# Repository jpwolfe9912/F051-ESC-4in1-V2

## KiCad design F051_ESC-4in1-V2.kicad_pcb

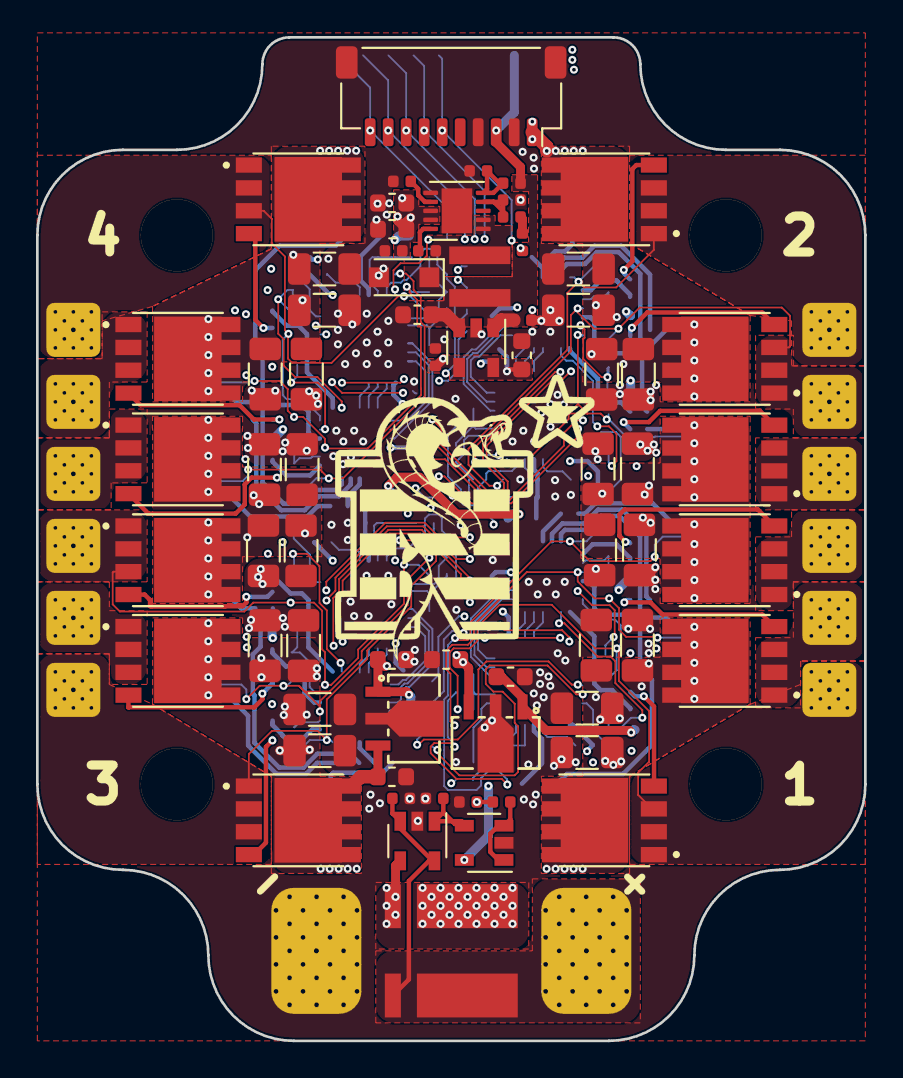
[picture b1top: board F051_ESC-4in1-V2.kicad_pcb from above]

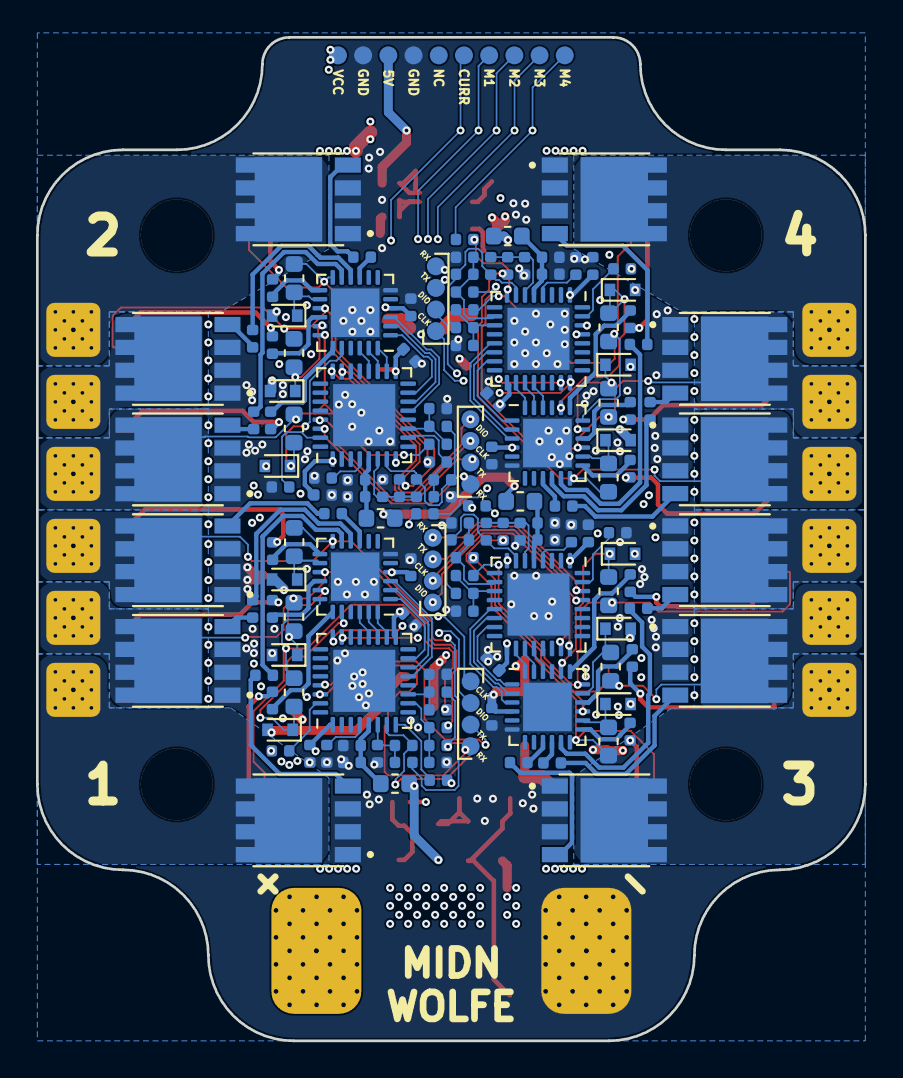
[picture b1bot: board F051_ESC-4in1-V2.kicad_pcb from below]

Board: 4 copper layers, 46.0 x 55.8 mm, 223 parts (149 on the bottom side), 164 nets.

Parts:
C1, C7, C13, C14, C15, C25, C26, C27, C28, C34, C35, C36, C37, C41, C47, C48, C49, C70, C74: 0.1uF; C_0402_1005Metric
C2, C3, C5, C6, C29, C30, C31, C38, C39, C40, C42, C43, C44, C69: 0.1uF; C_0603_1608Metric
C4, C68: 0.33uF; C_0603_1608Metric
C8: 3.3nF; C_0402_1005Metric
C9, C11, C23, C32, C45: 10nF; C_0402_1005Metric
C10, C12, C22, C33, C46: 1uF; C_0402_1005Metric
C16, C17, C18, C19, C20, C21, C50, C51, C52, C53, C54, C55, C56, C57, C58, C59, C60, C61, C62, C63, C64, C65, C66, C67: 47uF; C_1206_3216Metric
C24, C72, C73: 2.2uF; C_0603_1608Metric
C71: 22uF; C_0603_1608Metric
C75: 560pF; C_0402_1005Metric
C76: 2pF; C_0402_1005Metric
D1, D2, D3, D4, D5, D6, D7, D8, D9, D10, D11, D12: 250V; D_SOD-523
D13: 50V, 2A; D_SOD-123F
FB1, FB2, FB3, FB4: 100@100MHz; L_0603_1608Metric
H1, H2, H3, H4: MountingHole_Pad; MountingHole_4in1ESC
J1: Conn_01x02; Conn_PowerPad_4in1
J2: Conn_01x10; JST_SH_SM10B-SRSS-TB_1x10-1MP_P1.00mm_Horizontal
J3, J4, J5, J7: Conn_01x04; Conn_Debug
J6, J8, J10, J11: Conn_01x03; Conn_MotorPhase
J9: Conn_01x10; Conn_FC_Solder_10
L1: 12uH; L_XGL4030
Q1, Q2, Q3, Q4, Q5, Q6, Q7, Q8, Q9, Q10, Q11, Q12, Q13, Q14, Q15, Q16, Q17, Q18, Q19, Q20, Q21, Q22, Q23, Q24: TPH1R204PB
R1: 0m30; R_Shunt_Vishay_WSLP2726
R2: 60k; R_0402_1005Metric
R3: 500; R_0402_1005Metric
R4, R5, R6, R13, R14, R16, R17, R18, R19, R22, R26, R27, R38, R39, R40, R41, R43, R44, R61, R62, R63, R64, R66, R67: 10k; R_0402_1005Metric
R7, R8, R9, R10, R11, R12, R32, R33, R34, R35, R36, R37, R49, R50, R51, R52, R53, R54, R55, R56, R57, R58, R59, R60: 10; R_0402_1005Metric
R15, R20, R21, R23, R24, R25, R28, R29, R30, R31, R42, R45, R46, R47, R48, R65, R68, R69, R70, R71: 1k; R_0402_1005Metric
R73: 20k; R_0402_1005Metric
R74: 3.8k; R_0402_1005Metric
R76: 200k; R_0402_1005Metric
R77: 68k; R_0402_1005Metric
U1, U8, U10, U11: FD6288Q; QFN-24-1EP_4x4mm_P0.5mm_EP2.7x2.7mm
U2, U6, U9, U12: STM32F051K6Ux; QFN-32-1EP_5x5mm_P0.5mm_EP3.45x3.45mm
U3, U13: L78L12_SOT89; L78L12ACUTR
U4: LP2985-3.3; SOT-23-5
U5: INA139; SOT-23-5
U7: OPA340NA; SOT-23-5
U14: MP4560_QFN10; DFN-10-1EP_3x3mm_P0.5mm_EP1.7x2.5mm
U15: DTOM; DTOM_L

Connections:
+3.3VA_1: C11.1, C12.1, FB1.1, U2.5
+3.3VA_2: C9.1, C10.1, FB2.1, U6.5
+3.3VA_3: C32.1, C33.1, FB3.1, U9.5
+3.3VA_4: C45.1, C46.1, FB4.1, U12.5
+3V3: C13.1, C14.1, C23.1, C24.1, C25.1, C26.1, C34.1, C35.1, C47.1, C48.1, FB1.2, FB2.2, FB3.2, FB4.2, U2.1, U2.17, U4.4, U4.5, U6.1, U6.17, U7.5, U9.1, U9.17, U12.1, U12.17
+5V: C22.1, C71.1, J2.3, J9.3, L1.2, R73.1, U4.1, U4.3
+12V_1: C37.1, C41.1, C69.1, D7.2, D8.2, D9.2, D10.2, D11.2, D12.2, U10.4, U11.4, U13.1
+12V_2: C1.1, C5.1, C28.1, D1.2, D2.2, D3.2, D4.2, D5.2, D6.2, U1.4, U3.1, U8.4
/Curent Sense/CURR: C8.2, J2.6, J9.6, R3.1
/MCU 3/BOOT0: R48.1, U9.31
/MCU 3/HIN1: U9.18, U10.24
/MCU 3/HIN2: U9.19, U10.23
/MCU 3/LIN1: U9.15, U10.1
/MCU 3/LIN2: U9.14, U10.2
/MCU 3/LIN3: U9.13, U10.3
/MCU 3/NRST: C36.1, U9.4
/MCU 3/PhaseA: C38.2, J11.3, Q13.1, Q13.2, Q13.3, Q14.5, Q14.6, Q14.7, Q14.8, Q14.9, R38.2, U10.18
/MCU 3/PhaseB: C39.2, J11.2, Q15.1, Q15.2, Q15.3, Q16.5, Q16.6, Q16.7, Q16.8, Q16.9, R40.2, U10.15
/MCU 3/PhaseC: C40.2, J11.1, Q17.1, Q17.2, Q17.3, Q18.5, Q18.6, Q18.7, Q18.8, Q18.9, R43.2, U10.12
/MCU 3/SWCLK: J4.2, U9.24
/MCU 3/SWDIO: J4.1, U9.23
/MCU 3/SenseA: R38.1, R39.1, R45.2, U9.11
/MCU 3/SenseB: R40.1, R41.1, R46.2, U9.10
/MCU 3/SenseC: R43.1, R44.1, R47.2, U9.6
/MCU 3/SenseCOM: R39.2, R41.2, R44.2, U9.7
/MCU 3/USART1_RX: J4.4, U9.30
/MCU 3/USART1_TX: J4.3, U9.29
/MCU_1/BOOT0: R24.1, U2.31
/MCU_1/HIN1: U1.24, U2.18
/MCU_1/HIN2: U1.23, U2.19
/MCU_1/LIN1: U1.1, U2.15
/MCU_1/LIN2: U1.2, U2.14
/MCU_1/LIN3: U1.3, U2.13
/MCU_1/NRST: C15.1, U2.4
/MCU_1/PhaseA: C2.2, J6.3, Q1.1, Q1.2, Q1.3, Q2.5, Q2.6, Q2.7, Q2.8, Q2.9, R13.2, U1.18
/MCU_1/PhaseB: C3.2, J6.2, Q3.1, Q3.2, Q3.3, Q4.5, Q4.6, Q4.7, Q4.8, Q4.9, R16.2, U1.15
/MCU_1/PhaseC: C6.2, J6.1, Q5.1, Q5.2, Q5.3, Q6.5, Q6.6, Q6.7, Q6.8, Q6.9, R18.2, U1.12
/MCU_1/SWCLK: J3.1, U2.24
/MCU_1/SWDIO: J3.2, U2.23
/MCU_1/SenseA: R13.1, R14.1, R20.2, U2.11
/MCU_1/SenseB: R16.1, R17.1, R21.2, U2.10
/MCU_1/SenseC: R18.1, R19.1, R23.2, U2.6
/MCU_1/SenseCOM: R14.2, R17.2, R19.2, U2.7
/MCU_1/USART1_RX: J3.4, U2.30
/MCU_1/USART1_TX: J3.3, U2.29
/MCU_2/BOOT0: R31.1, U6.31
/MCU_2/HIN1: U6.18, U8.24
/MCU_2/HIN2: U6.19, U8.23
/MCU_2/LIN1: U6.15, U8.1
/MCU_2/LIN2: U6.14, U8.2
/MCU_2/LIN3: U6.13, U8.3
/MCU_2/NRST: C27.1, U6.4
/MCU_2/PhaseA: C29.2, J8.3, Q7.1, Q7.2, Q7.3, Q8.5, Q8.6, Q8.7, Q8.8, Q8.9, R4.2, U8.18
/MCU_2/PhaseB: C30.2, J8.2, Q9.1, Q9.2, Q9.3, Q10.5, Q10.6, Q10.7, Q10.8, Q10.9, R6.2, U8.15
/MCU_2/PhaseC: C31.2, J8.1, Q11.1, Q11.2, Q11.3, Q12.5, Q12.6, Q12.7, Q12.8, Q12.9, R26.2, U8.12
/MCU_2/SWCLK: J5.2, U6.24
/MCU_2/SWDIO: J5.1, U6.23
/MCU_2/SenseA: R4.1, R5.1, R28.2, U6.11
/MCU_2/SenseB: R6.1, R22.1, R29.2, U6.10
/MCU_2/SenseC: R26.1, R27.1, R30.2, U6.6
/MCU_2/SenseCOM: R5.2, R22.2, R27.2, U6.7
/MCU_2/USART1_RX: J5.4, U6.30
/MCU_2/USART1_TX: J5.3, U6.29
/MCU_4/BOOT0: R71.1, U12.31
/MCU_4/HIN1: U11.24, U12.18
/MCU_4/HIN2: U11.23, U12.19
/MCU_4/LIN1: U11.1, U12.15
/MCU_4/LIN2: U11.2, U12.14
/MCU_4/LIN3: U11.3, U12.13
/MCU_4/NRST: C49.1, U12.4
/MCU_4/PhaseA: C42.2, J10.3, Q19.1, Q19.2, Q19.3, Q20.5, Q20.6, Q20.7, Q20.8, Q20.9, R61.2, U11.18
/MCU_4/PhaseB: C43.2, J10.2, Q21.1, Q21.2, Q21.3, Q22.5, Q22.6, Q22.7, Q22.8, Q22.9, R63.2, U11.15
/MCU_4/PhaseC: C44.2, J10.1, Q23.1, Q23.2, Q23.3, Q24.5, Q24.6, Q24.7, Q24.8, Q24.9, R66.2, U11.12
/MCU_4/SWCLK: J7.1, U12.24
/MCU_4/SWDIO: J7.2, U12.23
/MCU_4/SenseA: R61.1, R62.1, R68.2, U12.11
/MCU_4/SenseB: R63.1, R64.1, R69.2, U12.10
/MCU_4/SenseC: R66.1, R67.1, R70.2, U12.6
/MCU_4/SenseCOM: R62.2, R64.2, R67.2, U12.7
/MCU_4/USART1_RX: J7.4, U12.30
/MCU_4/USART1_TX: J7.3, U12.29
/MOSFET Driver 3/HIN1: U9.20, U10.22
/MOSFET Driver 3/HO1: R49.2, U10.19
/MOSFET Driver 3/HO2: R51.2, U10.16
/MOSFET Driver 3/HO3: R53.2, U10.13
/MOSFET Driver 3/LO1: R50.2, U10.11
/MOSFET Driver 3/LO2: R52.2, U10.10
/MOSFET Driver 3/LO3: R54.2, U10.9
/MOSFET Driver 3/VB1: C38.1, D7.1, U10.20
/MOSFET Driver 3/VB2: C39.1, D8.1, U10.17
/MOSFET Driver 3/VB3: C40.1, D9.1, U10.14
/MOSFET_Driver_1/HIN1: U1.22, U2.20
/MOSFET_Driver_1/HO1: R7.2, U1.19
/MOSFET_Driver_1/HO2: R9.2, U1.16
/MOSFET_Driver_1/HO3: R11.2, U1.13
/MOSFET_Driver_1/LO1: R8.2, U1.11
/MOSFET_Driver_1/LO2: R10.2, U1.10
/MOSFET_Driver_1/LO3: R12.2, U1.9
/MOSFET_Driver_1/VB1: C2.1, D2.1, U1.20
/MOSFET_Driver_1/VB2: C3.1, D3.1, U1.17
/MOSFET_Driver_1/VB3: C6.1, D4.1, U1.14
/MOSFET_Driver_2/HIN1: U6.20, U8.22
/MOSFET_Driver_2/HO1: R32.2, U8.19
/MOSFET_Driver_2/HO2: R34.2, U8.16
/MOSFET_Driver_2/HO3: R36.2, U8.13
/MOSFET_Driver_2/LO1: R33.2, U8.11
/MOSFET_Driver_2/LO2: R35.2, U8.10
/MOSFET_Driver_2/LO3: R37.2, U8.9
/MOSFET_Driver_2/VB1: C29.1, D1.1, U8.20
/MOSFET_Driver_2/VB2: C30.1, D5.1, U8.17
/MOSFET_Driver_2/VB3: C31.1, D6.1, U8.14
/MOSFET_Driver_4/HIN1: U11.22, U12.20
/MOSFET_Driver_4/HO1: R55.2, U11.19
/MOSFET_Driver_4/HO2: R57.2, U11.16
/MOSFET_Driver_4/HO3: R59.2, U11.13
/MOSFET_Driver_4/LO1: R56.2, U11.11
/MOSFET_Driver_4/LO2: R58.2, U11.10
/MOSFET_Driver_4/LO3: R60.2, U11.9
/MOSFET_Driver_4/VB1: C42.1, D10.1, U11.20
/MOSFET_Driver_4/VB2: C43.1, D11.1, U11.17
/MOSFET_Driver_4/VB3: C44.1, D12.1, U11.14
/PWM_1: J2.7, J9.7, R15.2
/PWM_2: J2.8, J9.8, R25.2
/PWM_3: J2.9, J9.9, R42.2
/PWM_4: J2.10, J9.10, R65.2
GND: C1.2, C4.2, C5.2, C7.1, C8.1, C9.2, C10.2, C11.2, C12.2, C13.2, C14.2, C15.2, C16.1, C17.1, C18.1, C19.1, C20.1, C21.1, C22.2, C23.2, C24.2, C25.2, C26.2, C27.2, C28.2, C32.2, C33.2, C34.2, C35.2, C36.2, C37.2, C41.2, C45.2, C46.2, C47.2, C48.2, C49.2, C50.1, C51.1, C52.1, C53.1, C54.1, C55.1, C56.1, C57.1, C58.1, C59.1, C60.1, C61.1, C62.1, C63.1, C64.1, C65.1, C66.1, C67.1, C68.2, C69.2, C71.2, C72.2, C73.2, C74.2, C76.2, D13.2, H1.1, H2.1, H3.1, H4.1, J1.2, J2.2, J2.4, J9.2, J9.4, Q2.1, Q2.2, Q2.3, Q4.1, Q4.2, Q4.3, Q6.1, Q6.2, Q6.3, Q8.1, Q8.2, Q8.3, Q10.1, Q10.2, Q10.3, Q12.1, Q12.2, Q12.3, Q14.1, Q14.2, Q14.3, Q16.1, Q16.2, Q16.3, Q18.1, Q18.2, Q18.3, Q20.1, Q20.2, Q20.3, Q22.1, Q22.2, Q22.3, Q24.1, Q24.2, Q24.3, R2.2, R20.1, R21.1, R23.1, R24.2, R28.1, R29.1, R30.1, R31.2, R45.1, R46.1, R47.1, R48.2, R68.1, R69.1, R70.1, R71.2, R74.2, R76.2, R77.2, U1.6, U1.25, U2.33, U3.2, U4.2, U5.2, U6.33, U7.2, U8.6, U8.25, U9.33, U10.6, U10.25, U11.6, U11.25, U12.33, U13.2, U14.6
unnamed: C70.1, D13.1, L1.1, U14.1, U14.2
unnamed: C70.2, U14.10
unnamed: C75.1, C76.1, U14.4
unnamed: C75.2, R77.1
unnamed: Q1.4, R7.1
unnamed: Q2.4, R8.1
unnamed: Q3.4, R9.1
unnamed: Q4.4, R10.1
unnamed: Q5.4, R11.1
unnamed: Q6.4, R12.1
unnamed: Q7.4, R32.1
unnamed: Q8.4, R33.1
unnamed: Q9.4, R34.1
unnamed: Q10.4, R35.1
unnamed: Q11.4, R36.1
unnamed: Q12.4, R37.1
unnamed: Q13.4, R49.1
unnamed: Q14.4, R50.1
unnamed: Q15.4, R51.1
unnamed: Q16.4, R52.1
unnamed: Q17.4, R53.1
unnamed: Q18.4, R54.1
unnamed: Q19.4, R55.1
unnamed: Q20.4, R56.1
unnamed: Q21.4, R57.1
unnamed: Q22.4, R58.1
unnamed: Q23.4, R59.1
unnamed: Q24.4, R60.1
unnamed: R2.1, U5.1, U7.4
unnamed: R3.2, U7.1, U7.3
unnamed: R15.1, U2.8
unnamed: R25.1, U6.8
unnamed: R42.1, U9.8
unnamed: R65.1, U12.8
unnamed: R73.2, R74.1, U14.5
unnamed: R76.1, U14.7
VCC: C7.2, J1.1, R1.1, U5.3, U5.5
VCC_Shunt: C4.1, C16.2, C17.2, C18.2, C19.2, C20.2, C21.2, C50.2, C51.2, C52.2, C53.2, C54.2, C55.2, C56.2, C57.2, C58.2, C59.2, C60.2, C61.2, C62.2, C63.2, C64.2, C65.2, C66.2, C67.2, C68.1, C72.1, C73.1, C74.1, J2.1, J9.1, Q1.5, Q1.6, Q1.7, Q1.8, Q1.9, Q3.5, Q3.6, Q3.7, Q3.8, Q3.9, Q5.5, Q5.6, Q5.7, Q5.8, Q5.9, Q7.5, Q7.6, Q7.7, Q7.8, Q7.9, Q9.5, Q9.6, Q9.7, Q9.8, Q9.9, Q11.5, Q11.6, Q11.7, Q11.8, Q11.9, Q13.5, Q13.6, Q13.7, Q13.8, Q13.9, Q15.5, Q15.6, Q15.7, Q15.8, Q15.9, Q17.5, Q17.6, Q17.7, Q17.8, Q17.9, Q19.5, Q19.6, Q19.7, Q19.8, Q19.9, Q21.5, Q21.6, Q21.7, Q21.8, Q21.9, Q23.5, Q23.6, Q23.7, Q23.8, Q23.9, R1.2, U3.3, U5.4, U13.3, U14.8, U14.9

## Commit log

2021-03-22 Cleared front layer and rearranging
2021-03-22 More routing
2021-04-06 Lots of changes made with back being rerouted
2021-04-06 Started adding filtering caps
2021-04-07 More routing done
2021-04-08 Lots of routing done to get rid of no-connects. Down to 35 or so
2021-04-08 More traces routed. Down to 11 no-connects
2021-04-08 Finished routing all traces
2021-04-09 Finished adding vias and routing. Under review
2021-06-17 Added stuff

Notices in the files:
parts and their libraries:
Copyright 2016 Accelerated Designs. All rights reserved.
